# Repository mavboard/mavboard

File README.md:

mavboard
=================

Just got your MAVBoard? Check out the [Quickstart Guide](https://github.com/mavboard/mavboard/wiki/Getting-Started)!

The MAVBoard is a way to share a single MAVLink telemetry connection (the telemetry port on a 3D Robotics APM 2.X, for example) among multiple devices, such as OSDs, telemetry radios, telemetry converters or other add-on boards. Until now, the solution has been to create custom soldered cable harnesses which are difficult to make and not as flexible, since only one device can be connected to the "Tx" pin of the MAVLink connection.

The MAVBoard makes connecting several MAVLink devices a breeze. It is very easy to choose which device can access the "Tx" pin of the MAVLink connection by a simple jumper. Now your OSD, two-way telemetry radio AND FrSky telemetry can all run at the same time without the wiring being a nightmare!

The Pro model also includes on onboard Arduino compatible ATMega328P chip which has the ability to convert Mavlink data on the input into alternate RC telemetry protocols.

## Firmwares ##

This repository contains information about the MAVBoard hardware. There (will be) several firmwares that are compatible with the MAVBoard based on which RC system you use. Click below to go to the repository for the specific firmware to get instructions about how to use that firmware:

* FrSky Hub Protocol for D series Receivers (D4R-II, D8R-XP): [https://github.com/mavboard/jD-IOBoard](https://github.com/mavboard/jD-IOBoard)
* FrSky S.Port Protocol for X series Recievers (Taranis Compatible): (coming soon)
* OpenLRSng telemetry (throttled MAVLink): (coming soon)

## Typical Application ##

## Pinout ##

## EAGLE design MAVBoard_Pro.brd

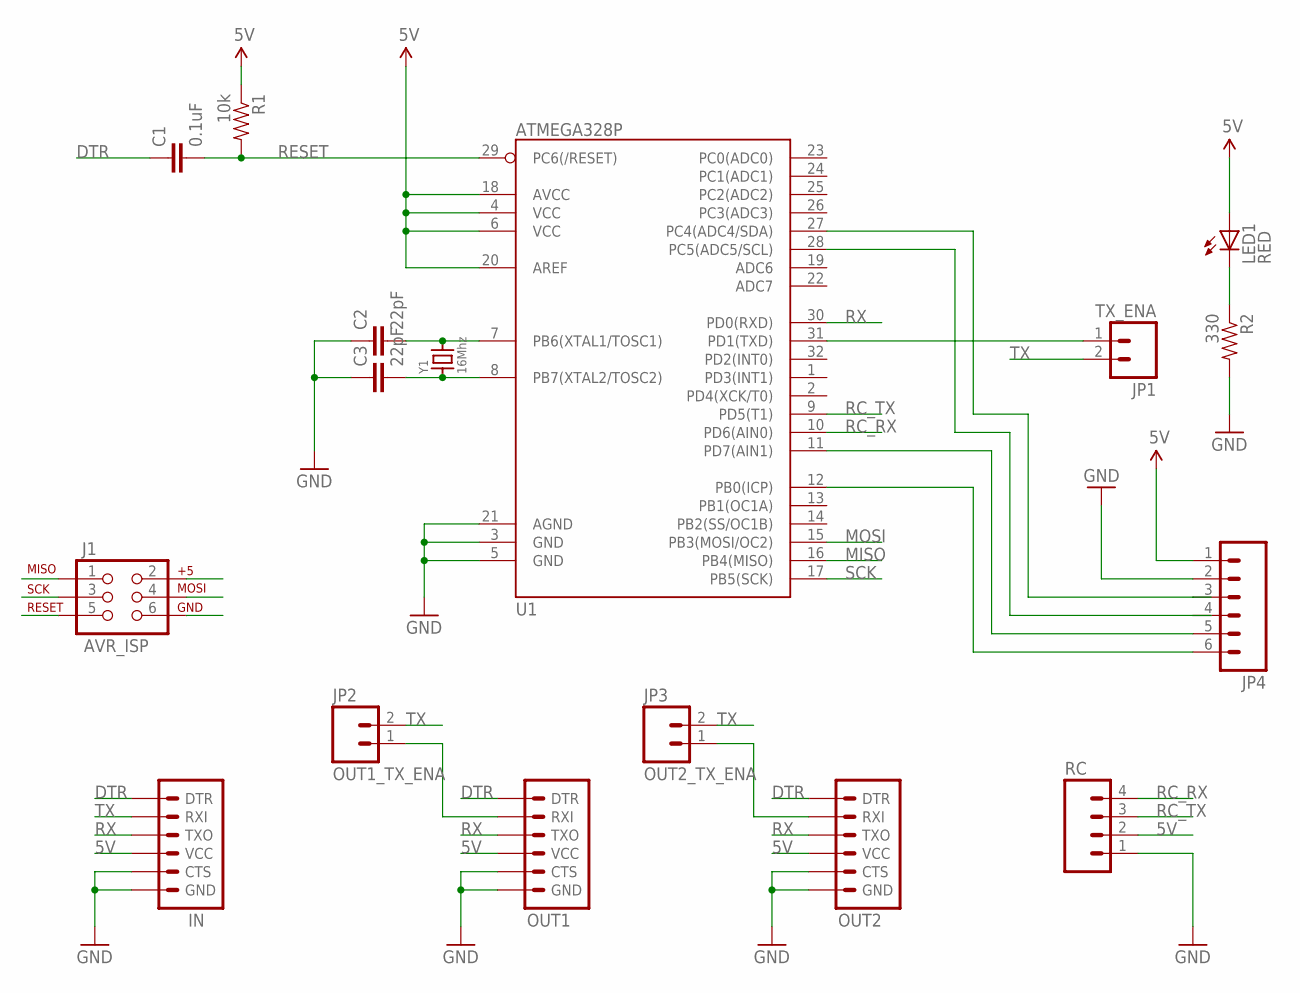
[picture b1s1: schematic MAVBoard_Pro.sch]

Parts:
C1: 0.1uF; 0603-CAP
C2, C3: 22pF; 0603-CAP
IN: ARDUINO_SERIAL_PROGRAMPTH; 1X06
J1: AVR_ISP; 2X3
JP1: TX_ENA; 1X02
JP2: OUT1_TX_ENA; 1X02
JP3: OUT2_TX_ENA; 1X02
JP4: M06SIP; 1X06
LED1: RED; LED-0603
OUT1, OUT2: ARDUINO_SERIAL_PROGRAMPTH; 1X06
R1: 10k; 0603-RES
R2: 330; 0603-RES
RC: M04PTH; 1X04
U1: ATMEGA328P; TQFP32-08
Y1: 16Mhz; CRYSTALSMD_5X3.2MM

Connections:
5V: IN.4 (VCC), J1.2, JP4.1, LED1.A, OUT1.4 (VCC), OUT2.4 (VCC), R1.1, RC.2, U1.4 (VCC), U1.6 (VCC), U1.18 (AVCC), U1.20 (AREF)
A4: JP4.3, U1.27 (PC4(ADC4/SDA))
A5: JP4.4, U1.28 (PC5(ADC5/SCL))
D7: JP4.5, U1.11 (PD7(AIN1))
D8: JP4.6, U1.12 (PB0(ICP))
DTR: C1.1, IN.1 (DTR), OUT1.1 (DTR), OUT2.1 (DTR)
GND: C2.1, C3.1, IN.5 (CTS), IN.6 (GND), J1.6, JP4.2, OUT1.5 (CTS), OUT1.6 (GND), OUT2.5 (CTS), OUT2.6 (GND), R2.2, RC.1, U1.3 (GND), U1.5 (GND), U1.21 (AGND)
MISO: J1.1, U1.16 (PB4(MISO))
MOSI: J1.4, U1.15 (PB3(MOSI/OC2))
unnamed: C2.2, U1.7 (PB6(XTAL1/TOSC1)), Y1.PIN3
unnamed: JP2.1, OUT1.2 (RXI)
unnamed: LED1.C, R2.1
unnamed: C3.2, U1.8 (PB7(XTAL2/TOSC2)), Y1.PIN1
unnamed: JP3.1, OUT2.2 (RXI)
unnamed: JP1.1, U1.31 (PD1(TXD))
RC_RX: RC.4, U1.10 (PD6(AIN0))
RC_TX: RC.3, U1.9 (PD5(T1))
RESET: C1.2, J1.5, R1.2, U1.29 (PC6(/RESET))
RX: IN.3 (TXO), OUT1.3 (TXO), OUT2.3 (TXO), U1.30 (PD0(RXD))
SCK: J1.3, U1.17 (PB5(SCK))
TX: IN.2 (RXI), JP1.2, JP2.2, JP3.2

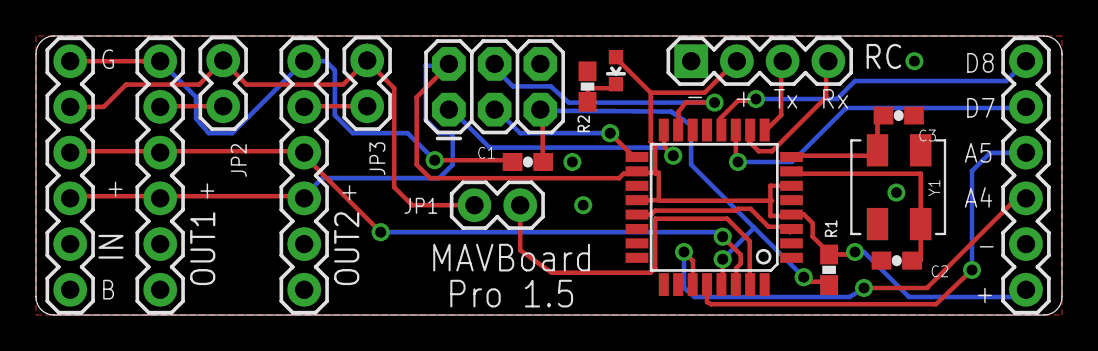
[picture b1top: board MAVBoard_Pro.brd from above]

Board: 2 copper layers, 57.0 x 15.5 mm, 18 parts (1 on the bottom side), 21 nets.

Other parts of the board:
U$3: OSHW_10X200_NOTEXT

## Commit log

2014-04-12 Eagle files
2014-04-21 added images
2014-04-22 More images

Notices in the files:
parts and their libraries:
SparkFun-DigitalIC: Licensing: CC v3.0 Share-Alike You are welcome to use this library for commercial purposes.
